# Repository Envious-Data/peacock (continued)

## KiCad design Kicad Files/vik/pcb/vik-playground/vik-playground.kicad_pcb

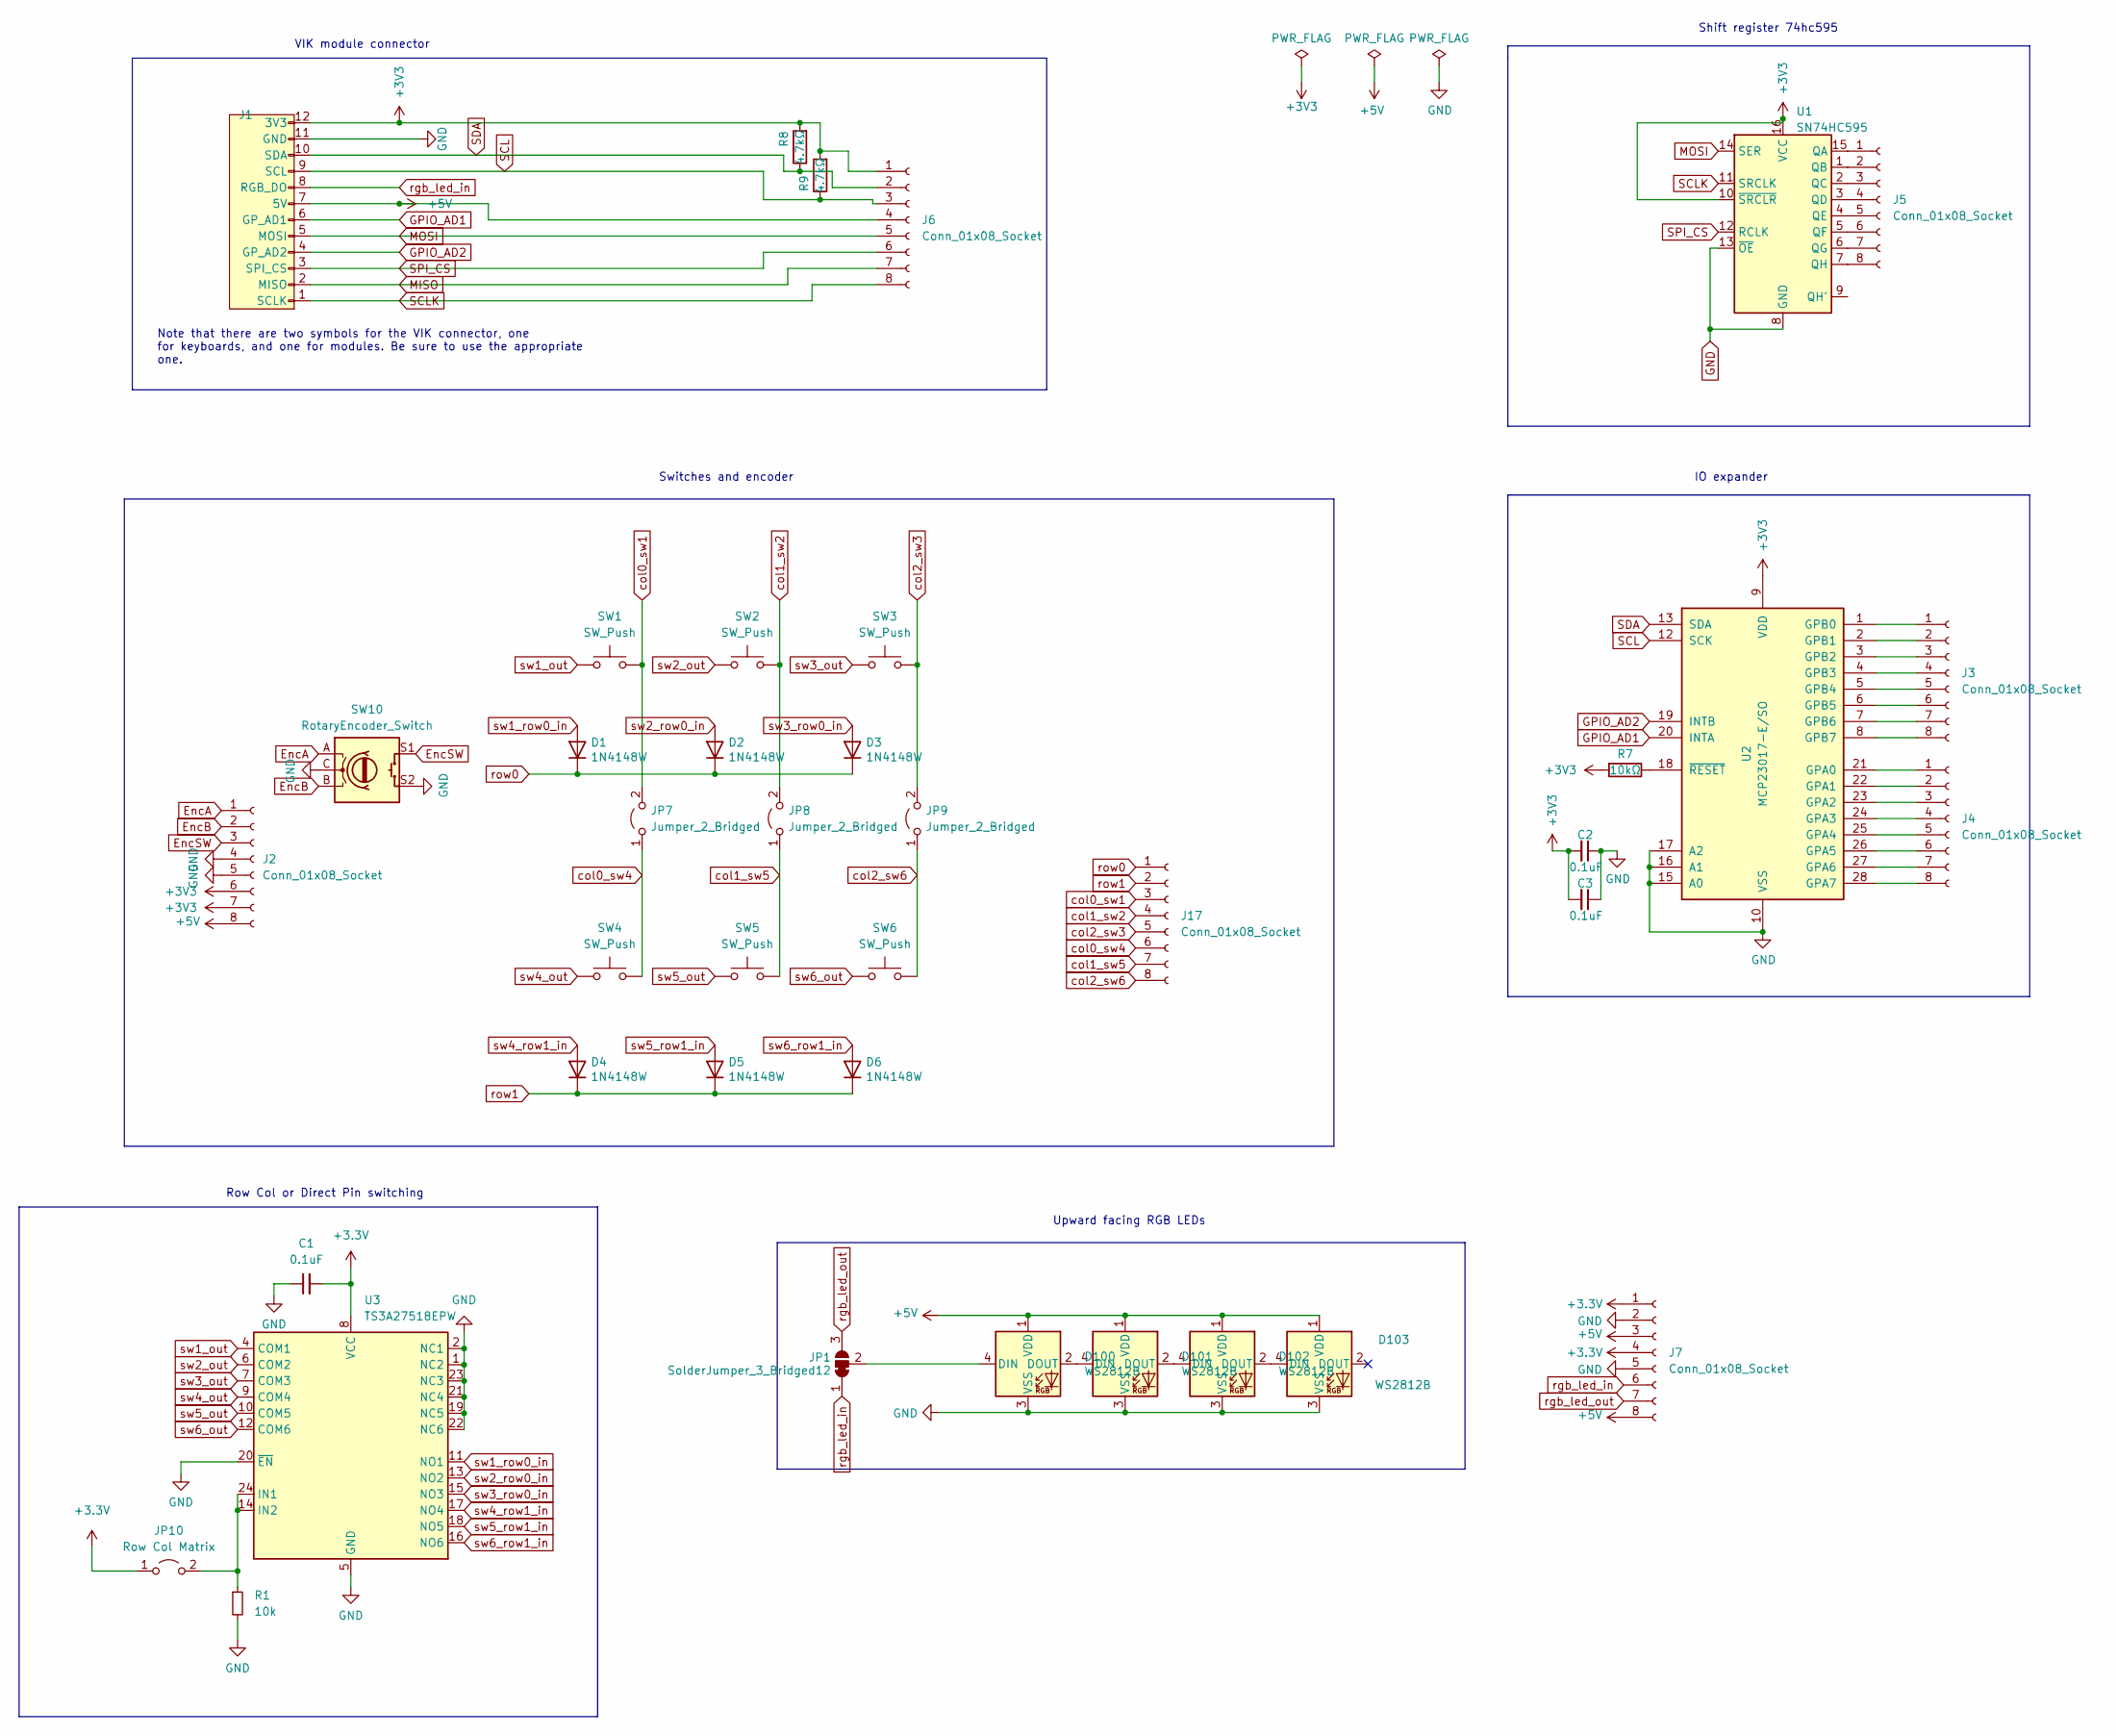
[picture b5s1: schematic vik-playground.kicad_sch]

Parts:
C1: 0.1uF; C_0805_2012Metric; LCSC C49678
C2, C3: 0.1uF; C_0805_2012Metric_Pad1.18x1.45mm_HandSolder; Part Name Capacitor; LCSC C49678
D1, D2, D3, D4, D5, D6: 1N4148W; D_SOD-123; LCSC C909967
D100, D101, D102, D103: WS2812B; LED_WS2812B_PLCC4_5.0x5.0mm_P3.2mm; LCSC C2761795
J1: vik-module-connector-horizontal; LCSC C479750
J2, J3, J4, J5, J6, J7, J17: Conn_01x08_Socket; PinSocket_1x08_P2.54mm_Vertical; LCSC C27438
JP1: SolderJumper_3_Bridged12; SolderJumper-3_P1.3mm_Bridged12_RoundedPad1.0x1.5mm
JP7, JP8, JP9: Jumper_2_Bridged; PinHeader_1x02_P2.00mm_Vertical
JP10: Row Col Matrix; PinHeader_1x02_P2.00mm_Vertical
R1: 10k; R_0805_2012Metric; LCSC C17414
R7: 10kΩ; R_0805_2012Metric_Pad1.20x1.40mm_HandSolder; Part Name Resistor; LCSC C17414
R8, R9: 4.7kΩ; R_0805_2012Metric_Pad1.20x1.40mm_HandSolder; Part Name Resistor; LCSC C17673
SW1, SW2, SW3, SW4, SW5, SW6: SW_Push; gateron-ks27-choc-v1-mx-soldered-and-hotswap
SW10: RotaryEncoder_Switch; RotaryEncoder_EC11-no-legs
U1: SN74HC595; SOIC-16_3.9x9.9mm_P1.27mm; LCSC C5947
U2: MCP23017-E/SO; SOIC-28W_7.5x17.9mm_P1.27mm; Part Name I/O Expander; LCSC C47023
U3: TS3A27518EPW; TSSOP-24_4.4x7.8mm_P0.65mm; LCSC C443721

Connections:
+5V: D100.1 (VDD), D101.1 (VDD), D102.1 (VDD), D103.1 (VDD), J1.7 (5V), J2.8, J6.4, J7.3, J7.8
EncA: J2.1, SW10.A
EncB: J2.2, SW10.B
EncSW: J2.3, SW10.S1
GND: C1.1, C2.1, C3.1, D100.3 (VSS), D101.3 (VSS), D102.3 (VSS), D103.3 (VSS), J1.11 (GND), J2.4, J2.5, J7.2, J7.5, R1.2, SW10.C, SW10.S2, U1.8 (GND), U1.13 (~OE), U2.10 (VSS), U2.15 (A0), U2.16 (A1), U2.17 (A2), U3.1 (NC2), U3.2 (NC1), U3.5 (GND), U3.19 (NC5), U3.20 (~EN), U3.21 (NC4), U3.22 (NC6), U3.23 (NC3)
GPIO_AD1: J1.6 (GPIO_AD1), U2.20 (INTA)
GPIO_AD2: J1.4 (GPIO_AD2), U2.19 (INTB)
MISO: J1.2 (MISO), J6.7
MOSI: J1.5 (MOSI), J6.5, U1.14 (SER)
unnamed: D100.4 (DIN), JP1.2 (C)
unnamed: D100.2 (DOUT), D101.4 (DIN)
unnamed: D101.2 (DOUT), D102.4 (DIN)
unnamed: D102.2 (DOUT), D103.4 (DIN)
unnamed: J3.1, U2.1 (GPB0)
unnamed: J3.2, U2.2 (GPB1)
unnamed: J3.3, U2.3 (GPB2)
unnamed: J3.4, U2.4 (GPB3)
unnamed: J3.5, U2.5 (GPB4)
unnamed: J3.6, U2.6 (GPB5)
unnamed: J3.7, U2.7 (GPB6)
unnamed: J3.8, U2.8 (GPB7)
unnamed: J4.1, U2.21 (GPA0)
unnamed: J4.2, U2.22 (GPA1)
unnamed: J4.3, U2.23 (GPA2)
unnamed: J4.4, U2.24 (GPA3)
unnamed: J4.5, U2.25 (GPA4)
unnamed: J4.6, U2.26 (GPA5)
unnamed: J4.7, U2.27 (GPA6)
unnamed: J4.8, U2.28 (GPA7)
unnamed: J5.1, U1.15 (QA)
unnamed: J5.2, U1.1 (QB)
unnamed: J5.3, U1.2 (QC)
unnamed: J5.4, U1.3 (QD)
unnamed: J5.5, U1.4 (QE)
unnamed: J5.6, U1.5 (QF)
unnamed: J5.7, U1.6 (QG)
unnamed: J5.8, U1.7 (QH)
unnamed: JP10.2 (B), R1.1, U3.14 (IN2), U3.24 (IN1)
unnamed: R7.1, U2.18 (~RESET)
SCL: J1.9 (SCL), J6.3, R9.1, U2.12 (SCK)
SCLK: J1.1 (SCLK), J6.8, U1.11 (SRCLK)
SDA: J1.10 (SDA), J6.2, R8.1, U2.13 (SDA)
SPI_CS: J1.3 (SPI_CS), J6.6, U1.12 (RCLK)
col0_sw1: J17.3, JP7.2 (B), SW1.2
col0_sw4: J17.6, JP7.1 (A), SW4.2
col1_sw2: J17.4, JP8.2 (B), SW2.2
col1_sw5: J17.7, JP8.1 (A), SW5.2
col2_sw3: J17.5, JP9.2 (B), SW3.2
col2_sw6: J17.8, JP9.1 (A), SW6.2
rgb_led_in: J1.8 (RGB_LED_IN), J7.6, JP1.1 (A)
rgb_led_out: J7.7, JP1.3 (B)
row0: D1.1 (K), D2.1 (K), D3.1 (K), J17.1
row1: D4.1 (K), D5.1 (K), D6.1 (K), J17.2
sw1_out: SW1.1, U3.4 (COM1)
sw1_row0_in: D1.2 (A), U3.11 (NO1)
sw2_out: SW2.1, U3.6 (COM2)
sw2_row0_in: D2.2 (A), U3.13 (NO2)
sw3_out: SW3.1, U3.7 (COM3)
sw3_row0_in: D3.2 (A), U3.15 (NO3)
sw4_out: SW4.1, U3.9 (COM4)
sw4_row1_in: D4.2 (A), U3.17 (NO4)
sw5_out: SW5.1, U3.10 (COM5)
sw5_row1_in: D5.2 (A), U3.18 (NO5)
sw6_out: SW6.1, U3.12 (COM6)
sw6_row1_in: D6.2 (A), U3.16 (NO6)

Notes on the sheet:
Row Col or Direct Pin switching
Shift register 74hc595
IO expander
Note that there are two symbols for the VIK connector, one for keyboards, and one for modules. Be sure to use the appropriate one.
Switches and encoder
Upward facing RGB LEDs
VIK module connector

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
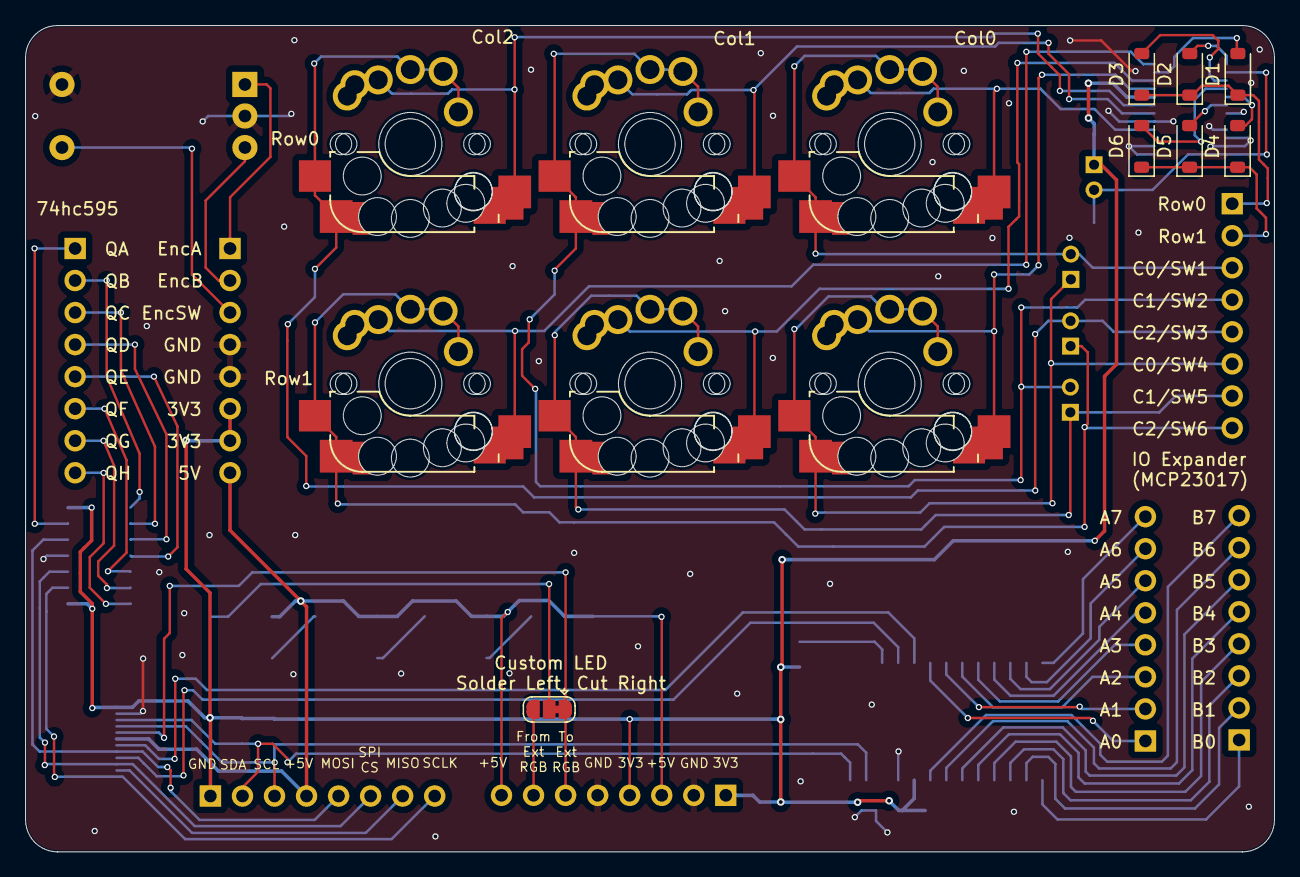
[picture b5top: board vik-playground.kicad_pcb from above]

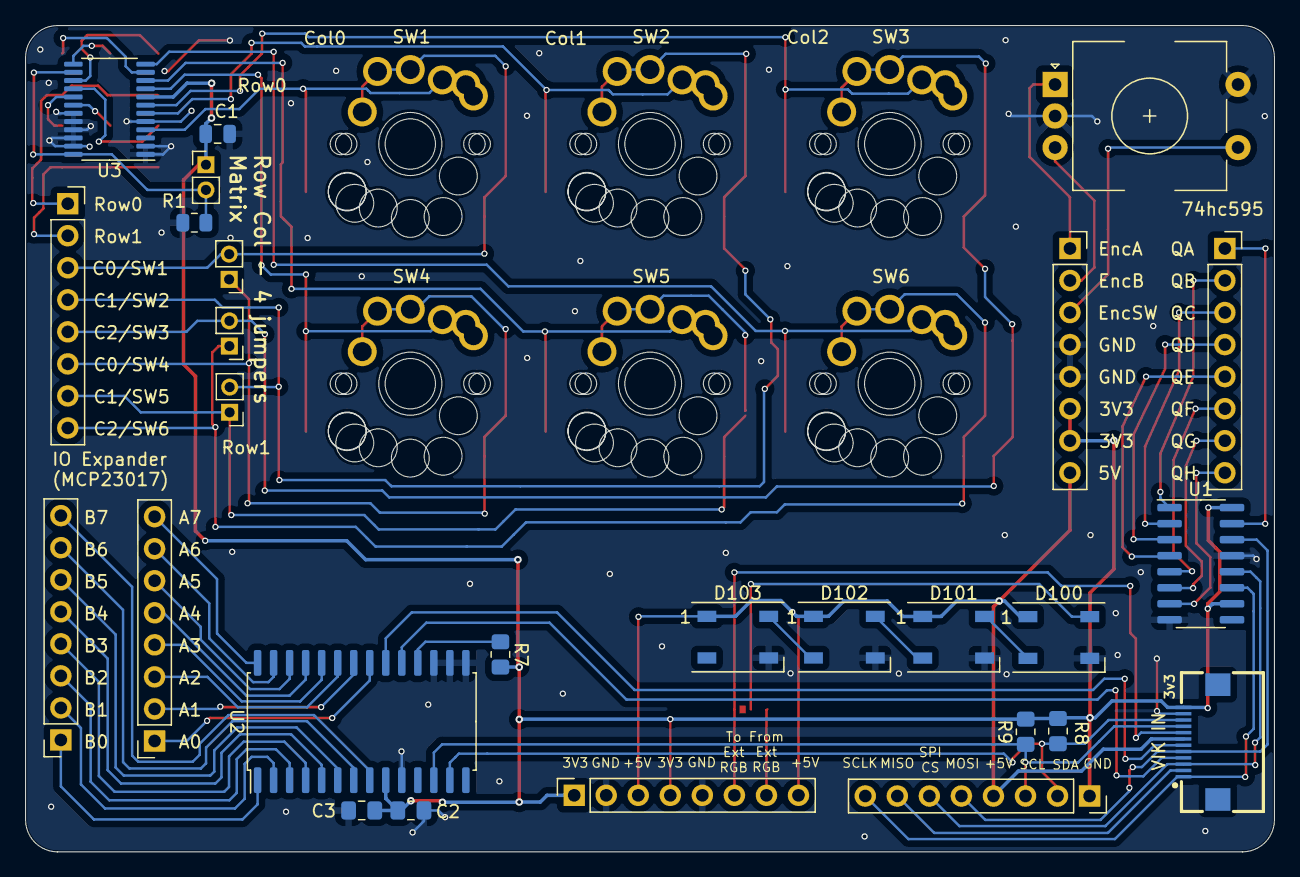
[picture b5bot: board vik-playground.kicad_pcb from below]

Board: 2 copper layers, 99.0 x 65.5 mm, 40 parts (33 on the bottom side), 66 nets.

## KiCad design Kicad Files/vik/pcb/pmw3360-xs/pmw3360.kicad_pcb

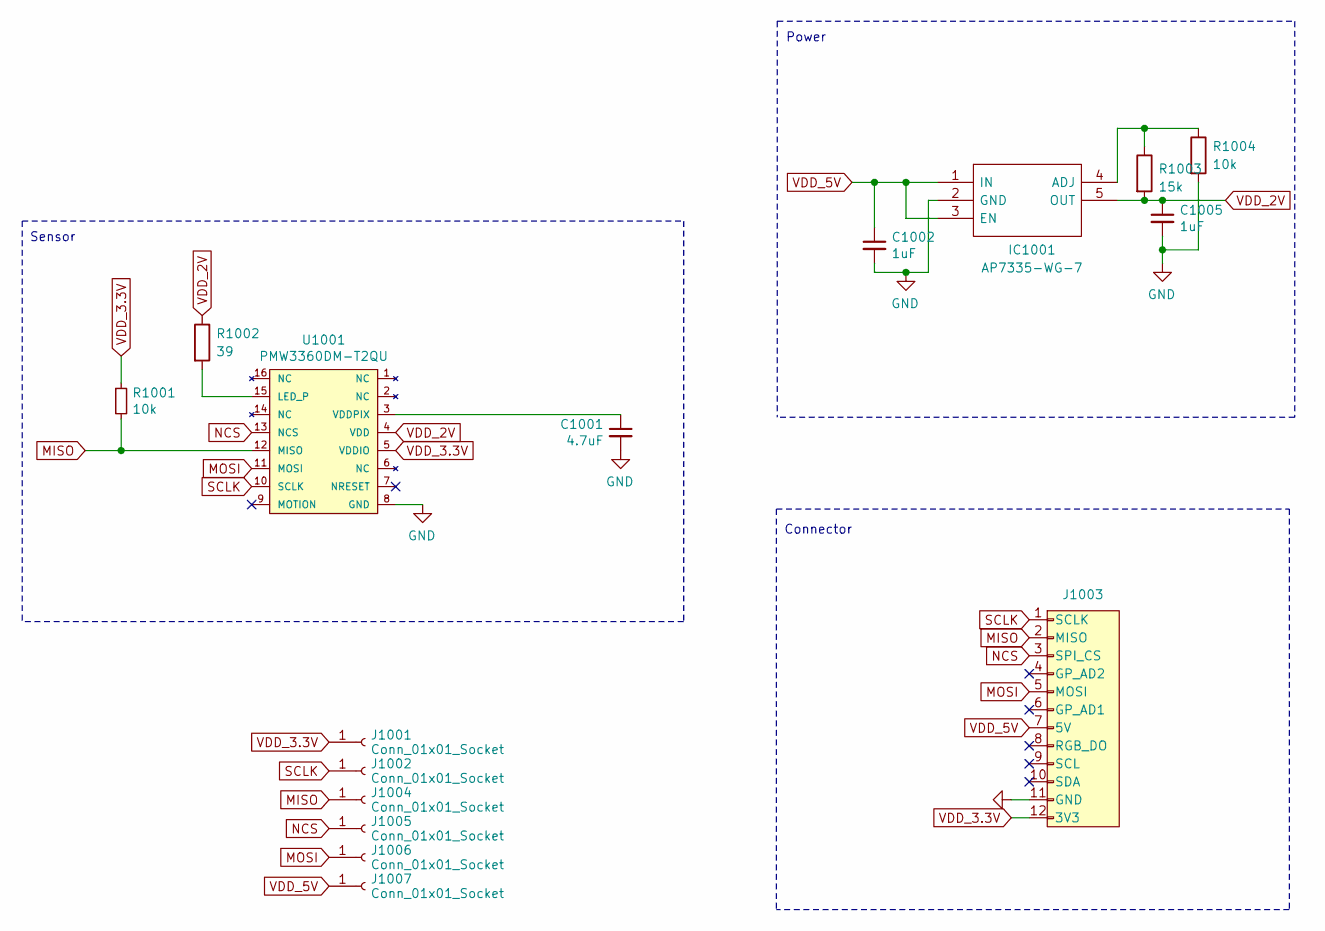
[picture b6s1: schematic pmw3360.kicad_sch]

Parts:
C1001: 4.7uF; C_0603_1608Metric; LCSC C19666
C1002, C1005: 1uF; C_0603_1608Metric; LCSC C15849
IC1001: AP7335-WG-7; SOT-23-5_HandSoldering; Manufacturer_Part_Number AP7331-WG-7; Mouser Part Number 621-AP7331-WG-7
J1001, J1002, J1004, J1005, J1006, J1007: Conn_01x01_Socket; SolderWire-0.5sqmm_1x01_D0.9mm_OD2.3mm
J1003: vik-module-connector-horizontal; LCSC C2919557
R1001, R1004: 10k; R_0603_1608Metric; LCSC C25804
R1002: 39; R_0603_1608Metric; LCSC C23154
R1003: 15k; R_0603_1608Metric; LCSC C22809
U1001: PMW3360DM-T2QU; DIP-16_W10.16mm

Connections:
GND: C1001.2, C1002.2, C1005.2, IC1001.2 (GND), J1003.11 (GND), R1004.2, U1001.8 (GND)
MISO: J1003.2 (MISO), J1004.1, R1001.2, U1001.12 (MISO)
MOSI: J1003.5 (MOSI), J1006.1, U1001.11 (MOSI)
NCS: J1003.3 (SPI_CS), J1005.1, U1001.13 (NCS)
unnamed: IC1001.4 (ADJ), R1003.1, R1004.1
unnamed: R1002.2, U1001.15 (LED_P)
unnamed: C1001.1, U1001.3 (VDDPIX)
SCLK: J1002.1, J1003.1 (SCLK), U1001.10 (SCLK)
VDD_2V: C1005.1, IC1001.5 (OUT), R1002.1, R1003.2, U1001.4 (VDD)
VDD_3.3V: J1001.1, J1003.12 (3V3), R1001.1, U1001.5 (VDDIO)
VDD_5V: C1002.1, IC1001.1 (IN), IC1001.3 (EN), J1003.7 (5V), J1007.1

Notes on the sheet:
Power
Sensor
Connector

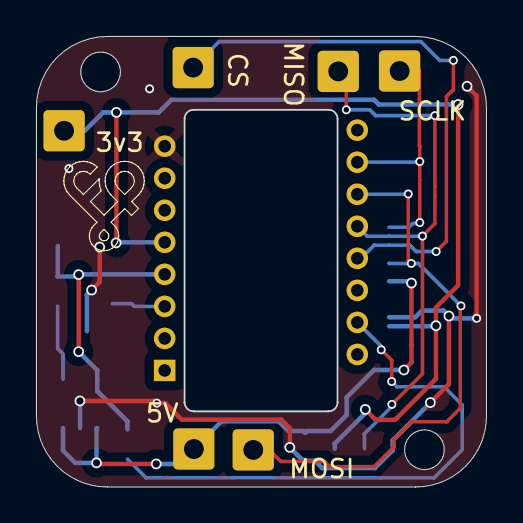
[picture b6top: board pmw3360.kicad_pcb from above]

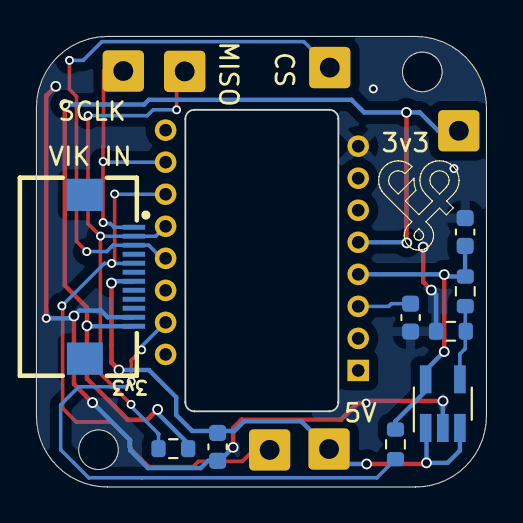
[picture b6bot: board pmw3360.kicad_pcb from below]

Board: 2 copper layers, 25.0 x 25.0 mm, 16 parts (10 on the bottom side), 11 nets.

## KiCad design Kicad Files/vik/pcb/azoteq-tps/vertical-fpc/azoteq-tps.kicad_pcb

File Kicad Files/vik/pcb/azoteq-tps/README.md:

# Azoteq Proxsense (TPSXX) VIK module

## Overview

This is a VIK module made to add a VIK connector to the [Azoteq Proxsense (TPSXX)](https://www.azoteq.com/images/stories/pdf/proxsense_i2c_trackpad_datasheet.pdf)(e.g. 43, 65) trackpads.

## Fabrication and BOM

For PCB fabrication, you can use the files in the production folder.

* gerbers.zip - the file used to fabricate the pcb
* bom.csv - used for PCBA. You can also use the part numbers in this file to look up the exact parts as [lcsc.com](https://lcsc.com)
* positions.csv - used for PCBA

Using the 3 files above, this has been tested at [jlcpcb.com](https://jlcpcb.com)

## VIK module certification

| Category                | Classification          | Response           |
| ----------------------- | ----------------------- | ------------------ |
| FPC connector           | Required                | :heavy_check_mark: |
| Breakout pins           | Recommended             | :x:                |
| Uses: SPI               | Optional                | :x:                |
| SPI used for SPI only   | Strongly recommended    | :x:                |
| Uses: I2C               | Optional                | :heavy_check_mark: |
| I2C used for I2C only   | Strongly Recommended    | :heavy_check_mark: |
| I2C pull ups            | Required                | :heavy_check_mark: |
| Uses: RGB               | Optional                | :x:                |
| Uses: Extra GPIO 1      | Optional                | :x:                |
| Uses: Extra GPIO 2      | Optional                | :x:                |
| Standard PCB Size/Mount | Strongly recommended    | :x:                |

## PCB images

### horizontal fpc

### vertical fpc

#### assembled vertical

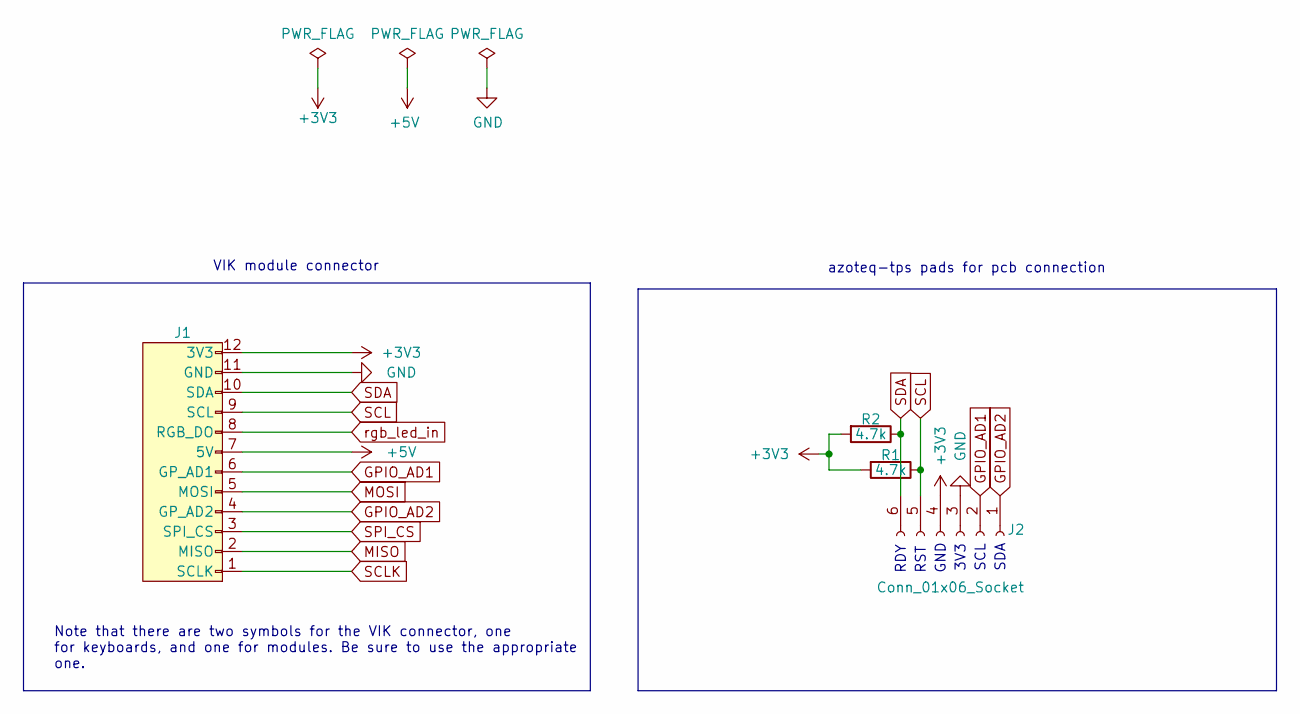
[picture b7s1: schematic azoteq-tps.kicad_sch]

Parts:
J1: vik-module-connector-vertical; LCSC C2919479
J2: Conn_01x06_Socket; Pad_06_2.00mm
R1, R2: 4.7k; R_0805_2012Metric_Pad1.20x1.40mm_HandSolder; LCSC C115310

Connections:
+3V3: J1.12 (3V3), J2.4, R1.2, R2.2
+5V: J1.7 (5V)
GND: J1.11 (GND), J2.3
GPIO_AD1: J1.6 (GPIO_AD1), J2.2
GPIO_AD2: J1.4 (GPIO_AD2), J2.1
MISO: J1.2 (MISO)
MOSI: J1.5 (MOSI)
SCL: J1.9 (SCL), J2.5, R1.1
SCLK: J1.1 (SCLK)
SDA: J1.10 (SDA), J2.6, R2.1
SPI_CS: J1.3 (SPI_CS)
rgb_led_in: J1.8 (RGB_LED_IN)

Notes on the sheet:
GND
RST
SCL
Note that there are two symbols for the VIK connector, one for keyboards, and one for modules. Be sure to use the appropriate one.
azoteq-tps pads for pcb connection
3V3
SDA
VIK module connector
RDY

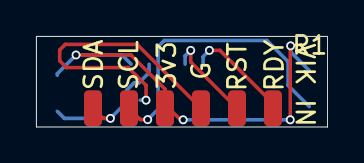
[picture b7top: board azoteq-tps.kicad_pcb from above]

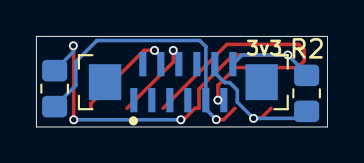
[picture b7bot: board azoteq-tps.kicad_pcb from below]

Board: 2 copper layers, 16.2 x 5.0 mm, 4 parts (3 on the bottom side), 6 nets.

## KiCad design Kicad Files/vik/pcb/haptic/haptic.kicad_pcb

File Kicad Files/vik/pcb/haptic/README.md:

# Haptic feedback module

## Overview

This is a VIK module made to house the [Pimoroni DRV2605L](https://shop.pimoroni.com/products/drv2605l-linear-actuator-haptic-breakout?variant=27859486867539) breakout board.

## Fabrication and BOM

For PCB fabrication, you can use the files in the production folder.

* gerbers.zip - the file used to fabricate the pcb
* bom.csv - used for PCBA. You can also use the part numbers in this file to look up the exact parts as [lcsc.com](https://lcsc.com)
* positions.csv - used for PCBA

Using the 3 files above, this has been tested at [jlcpcb.com](https://jlcpcb.com)

## VIK module certification

| Category                | Classification          | Response           |
| ----------------------- | ----------------------- | ------------------ |
| FPC connector           | Required                | :heavy_check_mark: |
| Breakout pins           | Recommended             | :x:                |
| Uses: SPI               | Optional                | :x:                |
| SPI used for SPI only   | Strongly recommended    | N/A                |
| Uses: I2C               | Optional                | :heavy_check_mark: |
| I2C used for I2C only   | Strongly Recommended    | :heavy_check_mark: |
| I2C pull ups            | Required                | 4.7kΩ              |
| Uses: RGB               | Optional                | :x:                |
| Uses: Extra GPIO 1      | Optional                | :x:                |
| Uses: Extra GPIO 2      | Optional                | :x:                |
| Standard PCB Size/Mount | Strongly recommended    | :x:                |

## PCB images

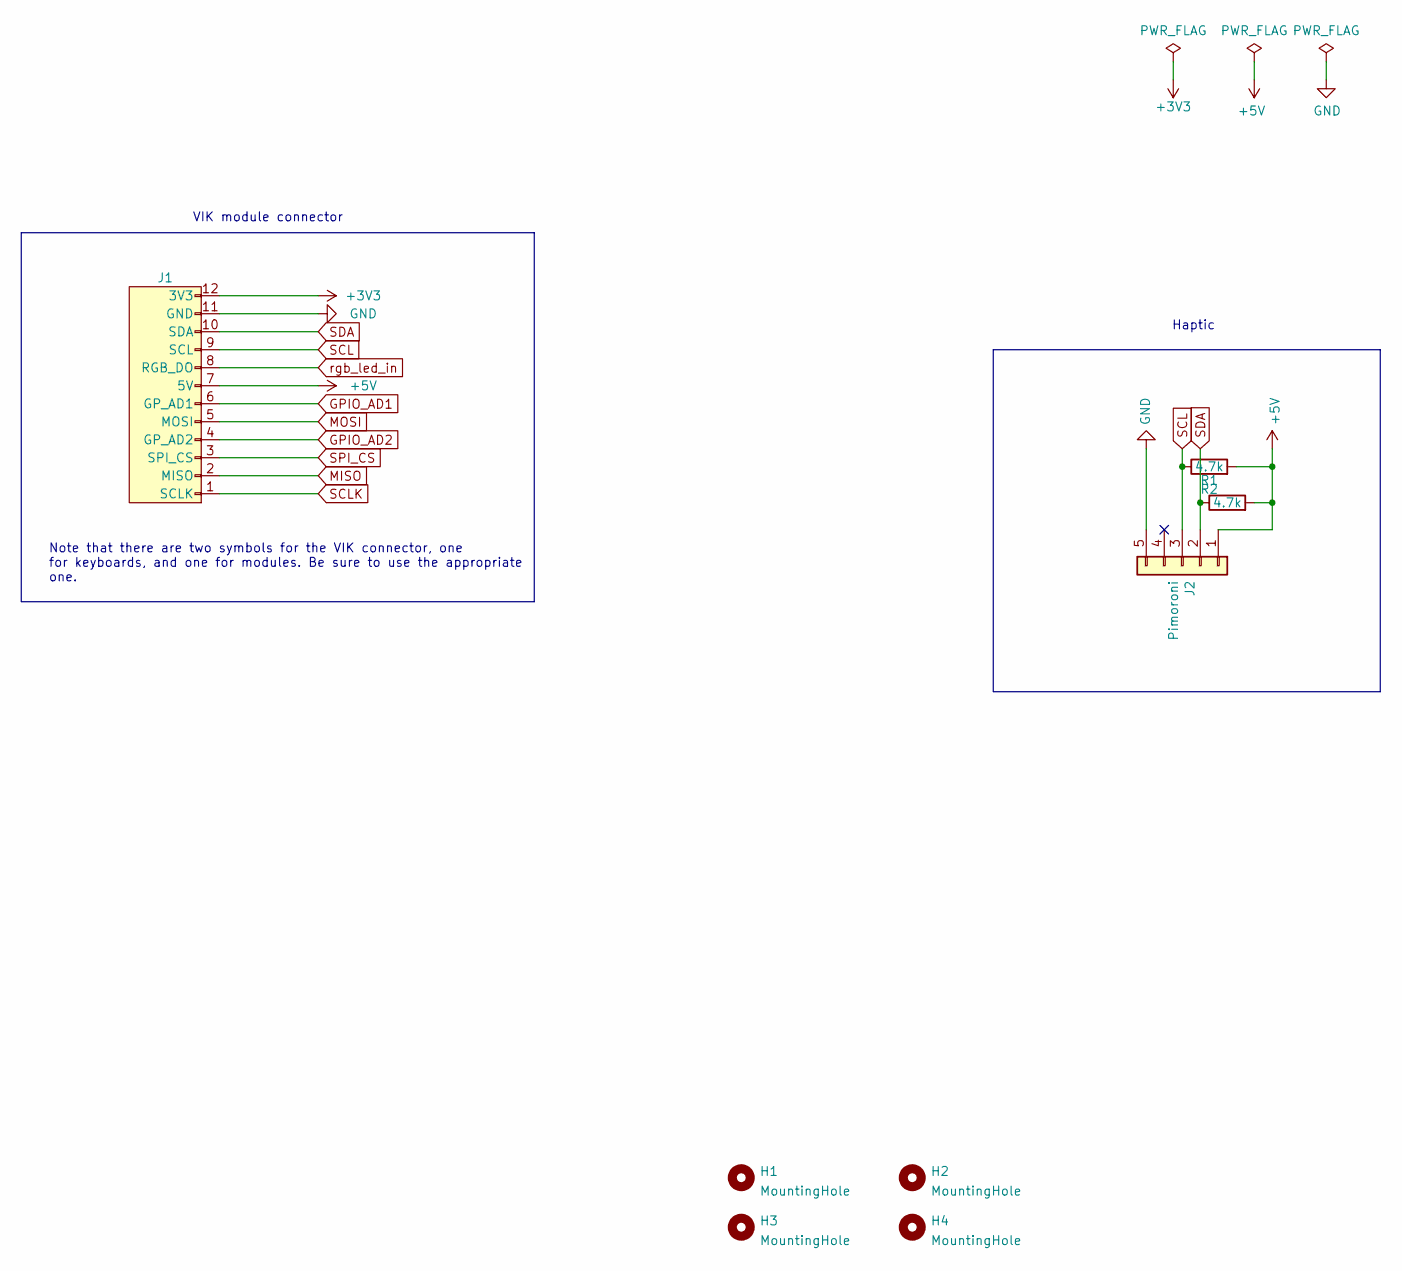
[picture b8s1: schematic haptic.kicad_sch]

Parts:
H1, H2, H3, H4: MountingHole; MountingHole_2.2mm_M2_DIN965_Pad
J1: vik-module-connector-horizontal; LCSC C479750
J2: Pimoroni; Pimoroni Haptic Buzz DRV2605L Driver
R1, R2: 4.7k; D3_TH_SMD; LCSC C104821

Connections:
+3V3: J1.12 (3V3)
+5V: J1.7 (5V), J2.1, R1.2, R2.2
GND: J1.11 (GND), J2.5
GPIO_AD1: J1.6 (GPIO_AD1)
GPIO_AD2: J1.4 (GPIO_AD2)
MISO: J1.2 (MISO)
MOSI: J1.5 (MOSI)
SCL: J1.9 (SCL), J2.3, R1.1
SCLK: J1.1 (SCLK)
SDA: J1.10 (SDA), J2.2, R2.1
SPI_CS: J1.3 (SPI_CS)
rgb_led_in: J1.8 (RGB_LED_IN)

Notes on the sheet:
Note that there are two symbols for the VIK connector, one for keyboards, and one for modules. Be sure to use the appropriate one.
VIK module connector
Haptic

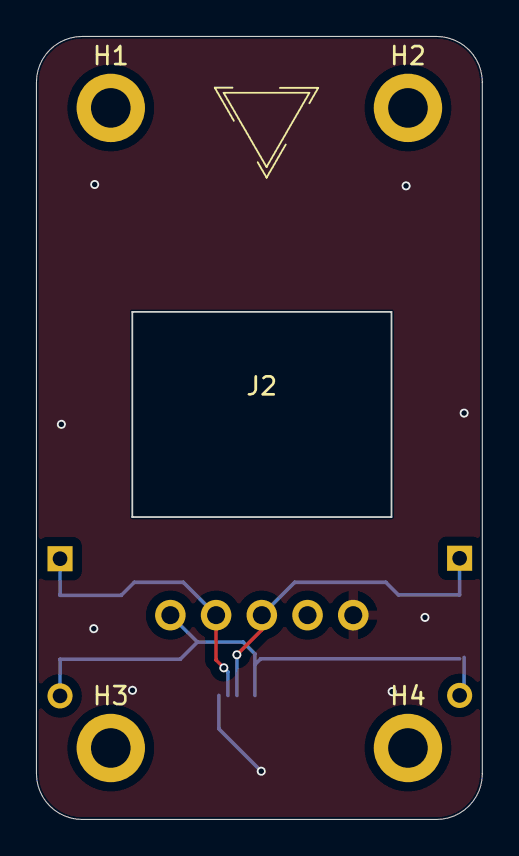
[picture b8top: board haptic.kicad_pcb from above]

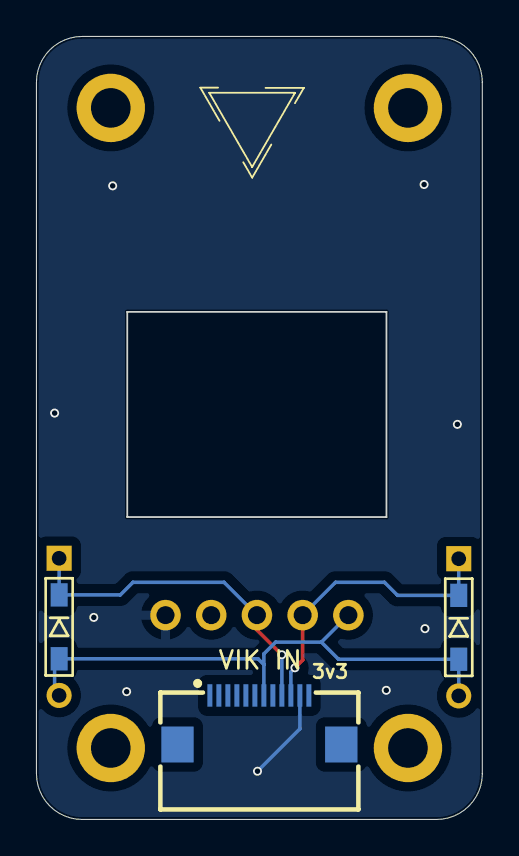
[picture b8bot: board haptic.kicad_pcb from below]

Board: 2 copper layers, 24.8 x 43.5 mm, 8 parts (3 on the bottom side), 4 nets.

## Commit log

2024-02-15 smashed everything into one PCB and removed some parts I don't want.
2024-02-15 made some adjustments to the gnd planes and connections
2024-02-15 rotated things in the PCB editor so its orientation matches intended use.
2024-03-19 added some art, might remove
2024-08-05 moved kicad files into their own folder
